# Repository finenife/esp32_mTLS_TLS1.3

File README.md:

# ESP32 mTLS Server Connection Guide
This document outlines the steps to set up an mTLS server connection using an ESP32 and Flask on a Raspberry Pi.
I'm using this repo to house some code for version control

# TODO Items 
1. Setup a admin process (base firmware image, admin UI with pyqt or similar) to enable PKI which potential use of to allow initial device certificate flashing for mTLS. 
    - Need a baseline firmware image that is expecting a connection to the Admin EXE, likely will need some symmetric encryption key burned into OTP (probably non-unique for simplicity, gotta have simplicity somewhere) 
    - I may end up building a small python QT application to allow an admin to login and provision the devices. Need to build an Admin EXE to allow a admin to setup the devices
    - Need to initialize an OIDC to be able to have an admin account that can be logged into (Keycloak)
    - Need to potentially consider using a container like EJBCA to handle PKI, maybe.

2. Setup a user front end. 
    - Registration
    - Avatar
    - Login
    - Preferences
    - Device Registration
    - Leaderboard etc. 

# Current Architecture 
## Device Hardware
1. Test Hardware ESP32-S3-WROOM-1U w/ externally attached wi-fi antenna.
2. Intention is to eventually develop a hardware module to integrate with [RAMN Project](https://github.com/ToyotaInfoTech/RAMN)

## Server Frontend 
1. User Frontend needs to be built...intending to build using Vue 3 framework. 

## Server Backend 
1. Ingress is handled by NGINX
2. Certificates are manually managed, issued, and signed currently using openssl as described below. 
3. Requests are currently all expected to be mTLS using a client certificate that is provisioned manually. 
4. Flask and uWSGI serve the backend. 
5. Sessions will be managed by Keycloak (self-hosted OIDC)
6. DB for keycloak and for flask will be 2 separate postgresql instances. 

## Potentially Helpful references
1. [Creating Server-side TLS certificates](https://jamielinux.com/docs/openssl-certificate-authority/create-the-root-pair.html)
2. [cipherlist.eu](https://cipherlist.eu/)
3. [Flask Flask guide](https://flask.palletsprojects.com/en/stable/)
4. [Vue QuickStart - Youtube Crash Course](https://youtu.be/1GNsWa_EZdw?si=PMYvQut2OosCF0Lm)
5. [Vue Flask Integration - Youtube Guide](https://youtu.be/lenV5aVOMp8?si=ouftit2TZEqHxVY5)
6. [EJBCA](https://www.ejbca.org/case/start-ejbca-docker-container-production-like-settings/)
7. [Keycloak](https://www.keycloak.org/server/containers)
8. [PostgreSQL](https://hub.docker.com/_/postgres)

## Current Building Dependencies to get mTLS requests to work from ESP32 to RPi: 
1. Another server to hit on local network (I used a raspberry pi 5 running latest pios lite)
2. Self-signed Certificate creation: completed using this guide:  https://jamielinux.com/docs/openssl-certificate-authority/create-the-root-pair.html
    - These certificates will ultimately be stored in a place where nginx and tests can access them. 
    - For a production application (which this is definitely not), follow your enterprise PKI procedures when creating/handling/updating any keys, and store your root key/cert offline. 
3. a super simple bare-bones python flask application - `Git: raspberrypi/flask/*` -> `Raspberrypi: ~/nginx/*`
```python
from flask import Flask
app = Flask(__name__)

@app.route("/")
def hello():
    return "<h1 style='color:blue'>Hello There!</h1>"

if __name__ == "__main__":
    app.run(host='0.0.0.0')
```

4. a simple uwsgi application for managing the flask app - `Git: raspberrypi/flask/wsgi.py`-> `Raspberrypi: ~/nginx/wsgi.py`
```python
  from myproject import app
  if __name__ == "__main__":
     app.run()
```
5. a uwsgi configuration file - `Git: raspberrypi/flask/myproject.ini`-> `Raspberrypi: ~/nginx/myproject.ini`
```
[uwsgi]
module = wsgi:app

master = true
processes = 5

socket = myproject.sock
uid = www-data
gid = www-data
chown-socket = www-data:www-data
chmod-socket = 660
vacuum = true

die-on-term = true
```
6. a systemd service for the flask application through uswgi - `Git: raspberrypi/flask/myproject.service`-> `Raspberrypi: /etc/systemd/system/myproject.service`
    - Do not forget to enable the service with `sudo systemctl enable myproject`
```
[Unit]
Description=uWSGI instance to serve myproject
After=network.target

[Service]
ProtectHome=false
WorkingDirectory=/home/hayden/nginx
Environment="PATH=/home/hayden/nginx/myprojectenv/bin"
ExecStart=/home/hayden/nginx/myprojectenv/bin/uwsgi --ini myproject.ini

[Install]
WantedBy=multi-user.target
```
7. Install `nginx` with `apt install nginx`
8. Run `sudo systemctl enable nginx` to make sure nginx starts up
9. NGINX server configuration on raspberry pi - `Git: raspberrypi/nginx/etc/*`-> `Raspberrypi: /etc/nginx/*` - /etc/nginx/sites-available/myproject
``` 
            server {
                 listen 443 ssl;
                  include snippets/self-signed.conf;
                  include snippets/ssl-params.conf;
                  location / {
                      if ($ssl_client_verify != SUCCESS){   // ssl_client_verify holds the result of ssl_verify_client
                           return 401 'blocked access to mTLS-protected resource';
                       }
                      include uwsgi_params;
                      uwsgi_pass unix:/home/hayden/nginx/myproject.sock;
                  }
              }
              server {
                  listen 80;
                  return 302 https://192.168.1.175;
              }
```
10. A small snippet file to allow nginx to know where to look for certificates, and where the private key it should use for TLS exchanges associated with the server-cert `Raspberrypi: /etc/nginx/snippets/self-signed.conf`
```
      ssl_certificate /etc/ssl/certs/intermediate/server.cert.pem;
      ssl_certificate_key /etc/ssl/private/intermediate/server.key.pem;
      ssl_client_certificate /etc/ssl/certs/intermediate/ca-chain.cert.pem;
```
11. A SSL/TLS configuration, SSL is used by nginx, but rest assured, it is TLS v1.3 `Raspberrypi: /etc/nginx/snippets/ssl-params.conf`
    - This was taken from [cipherlist.eu](https://cipherlist.eu/)
    - This only allows TLS1.3 connections, and only offers EECDH+AESGCM:EDH+AESGCM ciphers. 
```
      ssl_protocols TLSv1.3;
      ssl_prefer_server_ciphers on;
      ssl_dhparam /etc/nginx/dhparam.pem;
      ssl_ciphers EECDH+AESGCM:EDH+AESGCM;
      ssl_ecdh_curve secp384r1;
      ssl_session_timeout  10m;
      ssl_session_cache shared:SSL:10m;
      ssl_session_tickets off;
      ssl_stapling on;
      ssl_stapling_verify on;
      ssl_verify_client optional;               #This is where we tell nginx that we want to verify the client, setting optional allows some endpoints to not require mTLS. 
      resolver 8.8.8.8 8.8.4.4 valid=300s;
      resolver_timeout 5s;
      # Disable strict transport security for now. You can uncomment the following
      # line if you understand the implications.
      #add_header Strict-Transport-Security "max-age=63072000; includeSubDomains; preload";
      add_header X-Frame-Options DENY;
      add_header X-Content-Type-Options nosniff;
      add_header X-XSS-Protection "1; mode=block";
```
12. a nginx systemd service - `Git:raspberrypi/nginx/nginx.service`-> `Raspberrypi: /lib/systemd/system/nginx.service`
```
# Stop dance for nginx
# =======================
#
# ExecStop sends SIGQUIT (graceful stop) to the nginx process.
# If, after 5s (--retry QUIT/5) nginx is still running, systemd takes control
# and sends SIGTERM (fast shutdown) to the main process.
# After another 5s (TimeoutStopSec=5), and if nginx is alive, systemd sends
# SIGKILL to all the remaining processes in the process group (KillMode=mixed).
#
# nginx signals reference doc:
# http://nginx.org/en/docs/control.html
#
[Unit]
Description=A high performance web server and a reverse proxy server
Documentation=man:nginx(8)
After=network-online.target remote-fs.target nss-lookup.target
Wants=network-online.target

[Service]
ProtectHome=false
Type=forking
PIDFile=/run/nginx.pid
ExecStartPre=/usr/sbin/nginx -t -q -g 'daemon on; master_process on;'
ExecStart=/usr/sbin/nginx -g 'daemon on; master_process on;'
ExecReload=/usr/sbin/nginx -g 'daemon on; master_process on;' -s reload
ExecStop=-/sbin/start-stop-daemon --quiet --stop --retry QUIT/5 --pidfile /run/nginx.pid
TimeoutStopSec=5
KillMode=mixed
 
[Install]
WantedBy=multi-user.target
```

## Confirm Server is functioning
### Disable mTLS
- To start, lets disable mTLS checking and ensure that you have nginx setup correctly, comment out the following two lines in the files below: 
```
/etc/nginx/sites-available/myproject:
...
Line 6:                    if ($ssl_client_verify != SUCCESS){ 
```
and
```
/etc/nginx/snippets/ssl-params.conf:
...
Line 11:                   ssl_verify_client optional;
```

- **Note:** *With the certificates being self-signed certificates, you will want to ensure the ca-chain where the intermediate and root certificates are included is installed as a certificate on your machine. How to do this will be operating system specific and will not be included in this.*
- test your nginx configuration for any syntax errors with `sudo nginx -t`
- restart nginx with `sudo systemctl restart nginx`
- Attempt to connect to your raspberry pi by a web browser on the LAN and  you should see the following in your browser:
<h1 style='color:blue'>Hello There!</h1>

### Re-enable mTLS and install certs on the test client. 
- Now that you have confirmed the connection, ensure your client certificate, client private key, and the ca-chain are installed on your test machine correctly. Revert the nginx service change from above and readd the line to ensure mTLS verification. 
- test your nginx configuration for any syntax errors with `sudo nginx -t`
- restart nginx with `sudo systemctl restart nginx`
- Attempt to connect to your raspberry pi by a web browser on the same LAN as Raspberry Pi, and this time you should be prompted  and  you should see the following in your browser:
<h1 style='color:blue'>Hello There!</h1>

## Test with ESP32-s3
### Configure ESP-IDF Environment correctly.
The default env in espressif idf is looking for the following certs in the following path, all files should be pem format as output by guide noted above in pre-req #2
1. Server Validation CA Certificate Chain - /http-request/main/ca-chain.cert.pem 
2. The client issued certificate - /http-request/main/client.cert.pem
3. The client issed PEM Private Key (**Unencrypted**) - /http-request/main/client.plain.pem
    - This can be done by `openssl rsa -in {Path to encrypted_private_key.pem} -out {Path to decrypted_private_key.pem}`
    - You will be prompted for the original passphrase that was used when creating the cient key the first time. 
    - **Note:** *Your private key is very sensitive, and should only be known by the client. Follow appropriate best practices when handling private key material. ESP-IDF offers a method to store this with the protected password, but I was not able to get this function working before my initial commit. It is dangerous to have a plain text private key, and this should be avoided in production.*

### Build the image
Once the server is running, and the appropriate certificates are integrated here you can build with 
 - `idf.py build` - a configuration is provided for utilizing esp32-s3 in sdkconfig. 
 - `idf.py flash` - the sdkconfig is setup for flashing over uart, this can be changed with `idf.py menuconfig`
 - `idf.py monitor`
    - The serial console will prompt the user for wifi ssid and password from standard in, always pass it directly as `{SSID} {PWD}` with the space between. You wil not be able to see reply in the console. Press enter/return to submit. 

### Verify the connection
After running you will see the following: 

A TON of debug information, and then finally:

```
HTTP/1.1 200 OK
Server: nginx/1.22.1
Date: Fri, 15 Nov 2024 20:20:29 GMT
Content-Type: text/html; charset=utf-8
Content-Length: 40
Connection: keep-alive
X-Frame-Options: DENY
X-Content-Type-Options: nosniff
X-XSS-Protection: 1; mode=block

<h1 style='color:blue'>Hello There!</h1>
```

### This is the response we expected to see from our flask mTLS protected endpoint!

## Conclusion
This guide provides an overview of setting up an mTLS1.3 connection with ESP32, Nginx, and Flask. Follow each step carefully to ensure successful configuration. At time of writing this, I was able to see the output. This code is not intended, nor deployed in a production environment. I used this for my own learning and thought I would share openly here.

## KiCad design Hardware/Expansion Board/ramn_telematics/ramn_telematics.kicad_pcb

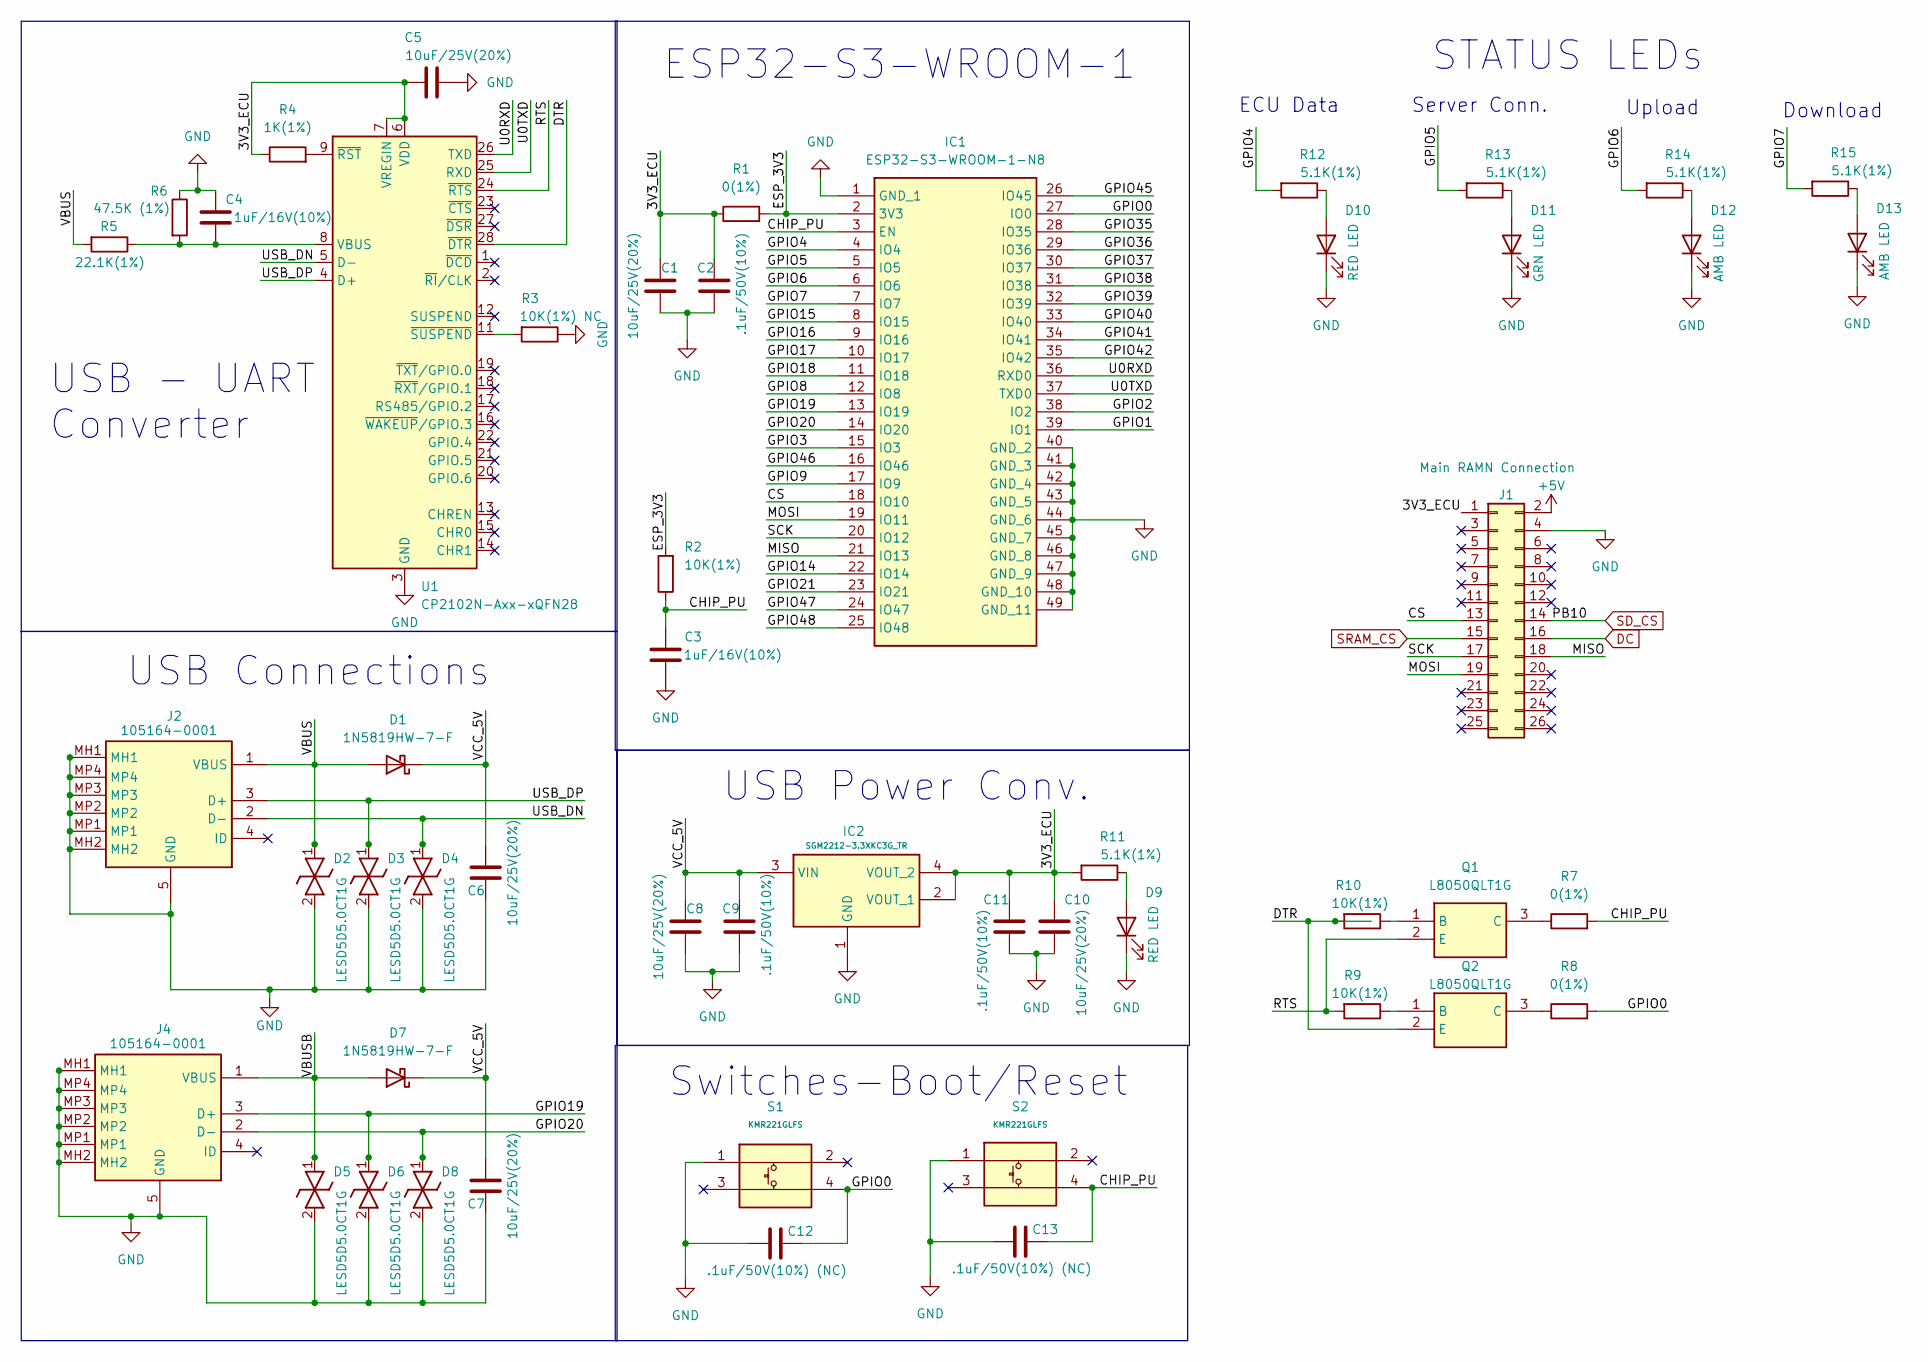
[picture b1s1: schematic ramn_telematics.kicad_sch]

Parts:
C1, C5, C8, C10: 10uF/25V(20%); C_0603_1608Metric; JLCPCB C76614
C2: .1uF/50V(10%); C_0603_1608Metric; JLCPCB C5673
C3, C4: 1uF/16V(10%); C_0603_1608Metric; JLCPCB C5673
C6: 10uF/25V(20%); C_0603_1608Metric; MFR.PART# C1608X5R1E106MT000E; JLCPCB# C76614
C7: 10uF/25V(20%); C_0603_1608Metric; JLCPCB# C76614
C9, C11: .1uF/50V(10%); C_0402_1005Metric
C12, C13: .1uF/50V(10%) (NC); C_0402_1005Metric
D1, D7: 1N5819HW-7-F; SOD3716X145N; Manufacturer_Part_Number 1N5819HW-7-F; Mouser Part Number 621-1N5819HW-F
D2, D3, D4, D5, D6, D8: LESD5D5.0CT1G; LESD5D50CT1G; Manufacturer_Part_Number LESD5D5.0CT1G
D9: RED LED; LED_0603_1608Metric; JLCPCB C79636
D10: RED LED; LED_0603_1608Metric; JLCPCB C79639
D11: GRN LED; LED_0603_1608Metric; JLCPCB C5123548
D12: AMB LED; LED_0603_1608Metric
D13: AMB LED; LED_0603_1608Metric; JLCPCB C264473
IC1: ESP32-S3-WROOM-1-N8; ESP32S3WROOM1N8R2; Manufacturer_Part_Number ESP32-S3-WROOM-1-N8
IC2: SGM2212-3.3XKC3G_TR; SOT230P700X180-4N; Manufacturer_Part_Number SGM2212-3.3XKC3G/TR
J1: Main RAMN Connection; PinHeader_2x13_P2.54mm_Vertical
J2, J4: 105164-0001; 1051640001; Manufacturer_Part_Number 105164-0001; Mouser Part Number 538-105164-0001
Q1, Q2: L8050QLT1G; Manufacturer_Part_Number L8050QLT1G; JLCPCB C49581
R1, R7, R8: 0(1%); R_0402_1005Metric
R2, R9, R10: 10K(1%); R_0402_1005Metric
R3: 10K(1%) NC; R_0402_1005Metric
R4: 1K(1%); R_0402_1005Metric
R5: 22.1K(1%); R_0402_1005Metric
R6: 47.5K (1%); R_0402_1005Metric
R11: 5.1K(1%); R_0402_1005Metric; JLCPCB C72044
R12, R13, R14, R15: 5.1K(1%); R_0402_1005Metric
S1, S2: KMR221GLFS; KMR221GLFS_PUSH_SMD_SWITCH_2.8mmx1.9mm; Manufacturer_Part_Number NTC013-AT1J-A160T
U1: CP2102N-Axx-xQFN28; QFN-28-1EP_5x5mm_P0.5mm_EP3.35x3.35mm

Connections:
+5V: J1.2
/3V3_ECU: C1.1, C2.1, C5.1, C10.1, C11.1, IC2.2 (VOUT_1), IC2.4 (VOUT_2), J1.1, R1.1, R4.1, R11.2, U1.6 (VDD), U1.7 (VREGIN)
/CHIP_PU: C3.1, C13.1, IC1.3 (EN), R2.1, R7.2, S2.4
/CS: IC1.18 (IO10), J1.13
/DTR: Q2.2 (E), R10.2, U1.28 (~DTR)
/ESP_3V3: IC1.2 (3V3), R1.2, R2.2
/GPIO0: C12.1, IC1.27 (IO0), R8.2, S1.4
/GPIO1: IC1.39 (IO1)
/GPIO2: IC1.38 (IO2)
/GPIO3: IC1.15 (IO3)
/GPIO4: IC1.4 (IO4), R12.2
/GPIO5: IC1.5 (IO5), R13.2
/GPIO6: IC1.6 (IO6), R14.2
/GPIO7: IC1.7 (IO7), R15.2
/GPIO8: IC1.12 (IO8)
/GPIO9: IC1.17 (IO9)
/GPIO14: IC1.22 (IO14)
/GPIO15: IC1.8 (IO15)
/GPIO16: IC1.9 (IO16)
/GPIO17: IC1.10 (IO17)
/GPIO18: IC1.11 (IO18)
/GPIO19: D6.1, IC1.13 (IO19), J4.3 (D+)
/GPIO20: D8.1, IC1.14 (IO20), J4.2 (D-)
/GPIO21: IC1.23 (IO21)
/GPIO35: IC1.28 (IO35)
/GPIO36: IC1.29 (IO36)
/GPIO37: IC1.30 (IO37)
/GPIO38: IC1.31 (IO38)
/GPIO39: IC1.32 (IO39)
/GPIO40: IC1.33 (IO40)
/GPIO41: IC1.34 (IO41)
/GPIO42: IC1.35 (IO42)
/GPIO45: IC1.26 (IO45)
/GPIO46: IC1.16 (IO46)
/GPIO47: IC1.24 (IO47)
/GPIO48: IC1.25 (IO48)
/MISO: IC1.21 (IO13), J1.18
/MOSI: IC1.19 (IO11), J1.19
/RTS: Q1.2 (E), R9.2, U1.24 (~RTS)
/SCK: IC1.20 (IO12), J1.17
/U0RXD: IC1.36 (RXD0), U1.26 (TXD)
/U0TXD: IC1.37 (TXD0), U1.25 (RXD)
/USB_DN: D4.1, J2.2 (D-), U1.5 (D-)
/USB_DP: D3.1, J2.3 (D+), U1.4 (D+)
/VBUS: D1.2 (A), D2.1, J2.1 (VBUS), R5.2
/VBUSB: D5.1, D7.2 (A), J4.1 (VBUS)
/VCC_5V: C6.2, C7.2, C8.1, C9.1, D1.1 (K), D7.1 (K), IC2.3 (VIN)
DC: J1.16
GND: C1.2, C2.2, C3.2, C4.1, C5.2, C6.1, C7.1, C8.2, C9.2, C10.2, C11.2, C12.2, C13.2, D2.2, D3.2, D4.2, D5.2, D6.2, D8.2, D9.1 (K), D10.1 (K), D11.1 (K), D12.1 (K), D13.1 (K), IC1.1 (GND_1), IC1.40 (GND_2), IC1.41 (GND_3), IC1.42 (GND_4), IC1.43 (GND_5), IC1.44 (GND_6), IC1.45 (GND_7), IC1.46 (GND_8), IC1.47 (GND_9), IC1.48 (GND_10), IC1.49 (GND_11), IC2.1 (GND), J1.4, J2.5 (GND), J2.MH1, J2.MH2, J2.MP1, J2.MP2, J2.MP3, J2.MP4, J4.5 (GND), J4.MH1, J4.MH2, J4.MP1, J4.MP2, J4.MP3, J4.MP4, R3.1, R6.1, S1.1, S2.1, U1.3 (GND), U1.29 (GND)
unnamed: D9.2 (A), R11.1
unnamed: D10.2 (A), R12.1
unnamed: D11.2 (A), R13.1
unnamed: D12.2 (A), R14.1
unnamed: D13.2 (A), R15.1
unnamed: Q1.1 (B), R10.1
unnamed: Q1.3 (C), R7.1
unnamed: Q2.1 (B), R9.1
unnamed: Q2.3 (C), R8.1
unnamed: C4.2, R5.1, R6.2, U1.8 (VBUS)
unnamed: R4.2, U1.9 (~RST)
unnamed: R3.2, U1.11 (~SUSPEND)
SD_CS: J1.14
SRAM_CS: J1.15

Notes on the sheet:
Server Conn.
Download
Upload
STATUS LEDs
USB - UART Converter
USB Connections
ESP32-S3-WROOM-1
ECU Data
USB Power Conv.
Switches-Boot/Reset

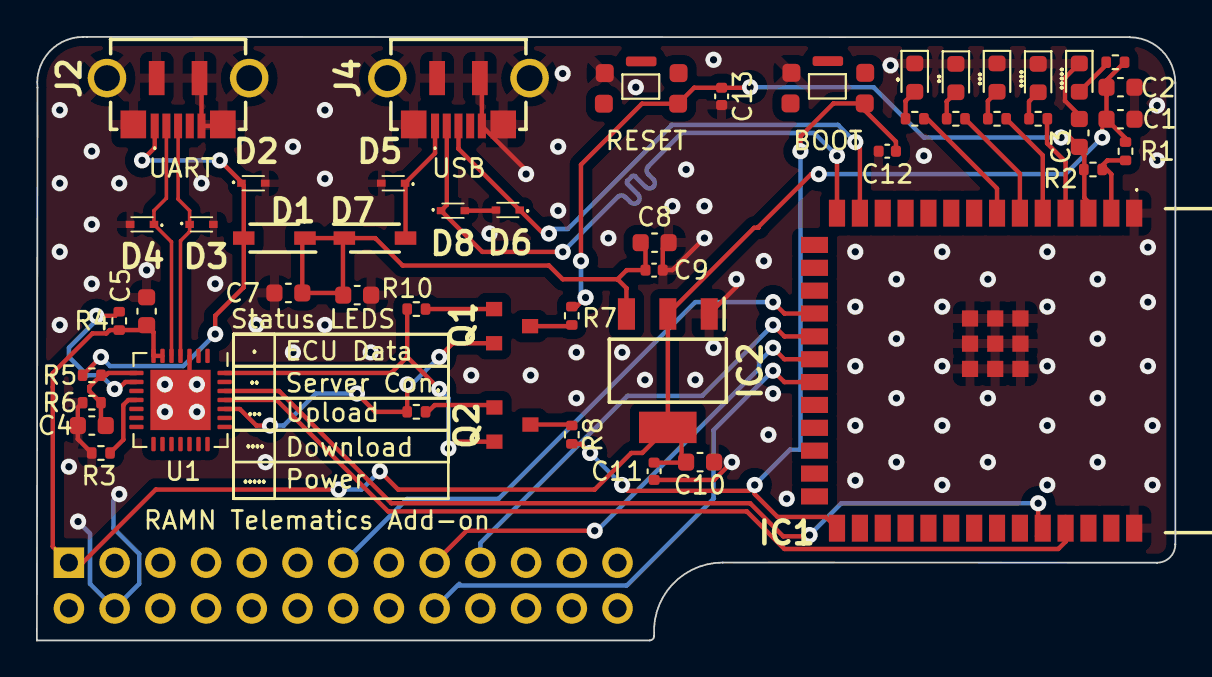
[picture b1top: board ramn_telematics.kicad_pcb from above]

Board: 2 copper layers, 63.2 x 33.5 mm, 51 parts (1 on the bottom side), 36 nets.

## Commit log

2024-11-17 Initial Commit
    This repo outlines the steps to set up an mTLS server connection using an ESP32, Nginx, and Flask on a Raspberry Pi over TLS1.3.
2024-11-17 fixing some initial readme stuff
2024-11-18 Some Initial Board Design
    - Reference: https://dl.espressif.com/dl/schematics/SCH_ESP32-S3-DevKitC-1_V1.1_20221130.pdf
    - Reference: https://dl.espressif.com/dl/schematics/PCB_ESP32-S3-DevKitC-1_V1.1_20220429.pdf
    - Reference: https://github.com/ToyotaInfoTech/RAMN/tree/main
2024-11-20 More Board Revisions
    Trying to update to components that are available in JLCPCB
2024-12-08 Update Readme.md
    Adding some TODO Items to the readme to ensure thoughts aren't lost, added several front end references for when I'm working on this again. Going to try and learn/play with the Vue js framework.
2024-12-11 Initial Vue/Tailwind Frontend Commits
2024-12-12 Initial building out of an admin page
    Wanted to build out an admin page for actually watching the status of the event and users and who is doing what, maybe some help with setup for future events etc.
2024-12-12 small bug fixes in tailwind
2024-12-14 Adding keycloak login, and session control in front end
    adding keycloak login wrapper around the application.
    started to integrate axios
2024-12-14 Vue/Flask/Keycloak Integration
    Frontend to Backend request JWT and with keycloak as IAM
2024-12-14 Implemented JWK caching
2024-12-14 added cache, tested multiple users
2024-12-14 making jwt auth a decorator
    made @jwt_required a decorator to ensure code readability
2024-12-14 avatar icon chooser, still in progress.
